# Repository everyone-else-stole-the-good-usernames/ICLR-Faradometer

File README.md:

```
_____     _       ____        _      ____      U  ___ u  __  __  U _____ u  _____  U _____ u   ____     
 |" ___|U  /"\  uU |  _"\ u U  /"\  u |  _"\      \/"_ \/U|' \/ '|u\| ___"|/ |_ " _| \| ___"|/U |  _"\ u  
U| |_  u \/ _ \/  \| |_) |/  \/ _ \/ /| | | |     | | | |\| |\/| |/ |  _|"     | |    |  _|"   \| |_) |/  
\|  _|/  / ___ \   |  _ <    / ___ \ U| |_| |\.-,_| |_| | | |  | |  | |___    /| |\   | |___    |  _ <    
 |_|    /_/   \_\  |_| \_\  /_/   \_\ |____/ u \_)-\___/  |_|  |_|  |_____|  u |_|U   |_____|   |_| \_\   
 )(\\,-  \\    >>  //   \\_  \\    >>  |||_         \\   <<,-,,-.   <<   >>  _// \\_  <<   >>   //   \\_  
(__)(_/ (__)  (__)(__)  (__)(__)  (__)(__)_)       (__)   (./  \.) (__) (__)(__) (__)(__) (__) (__)  (__) 

```

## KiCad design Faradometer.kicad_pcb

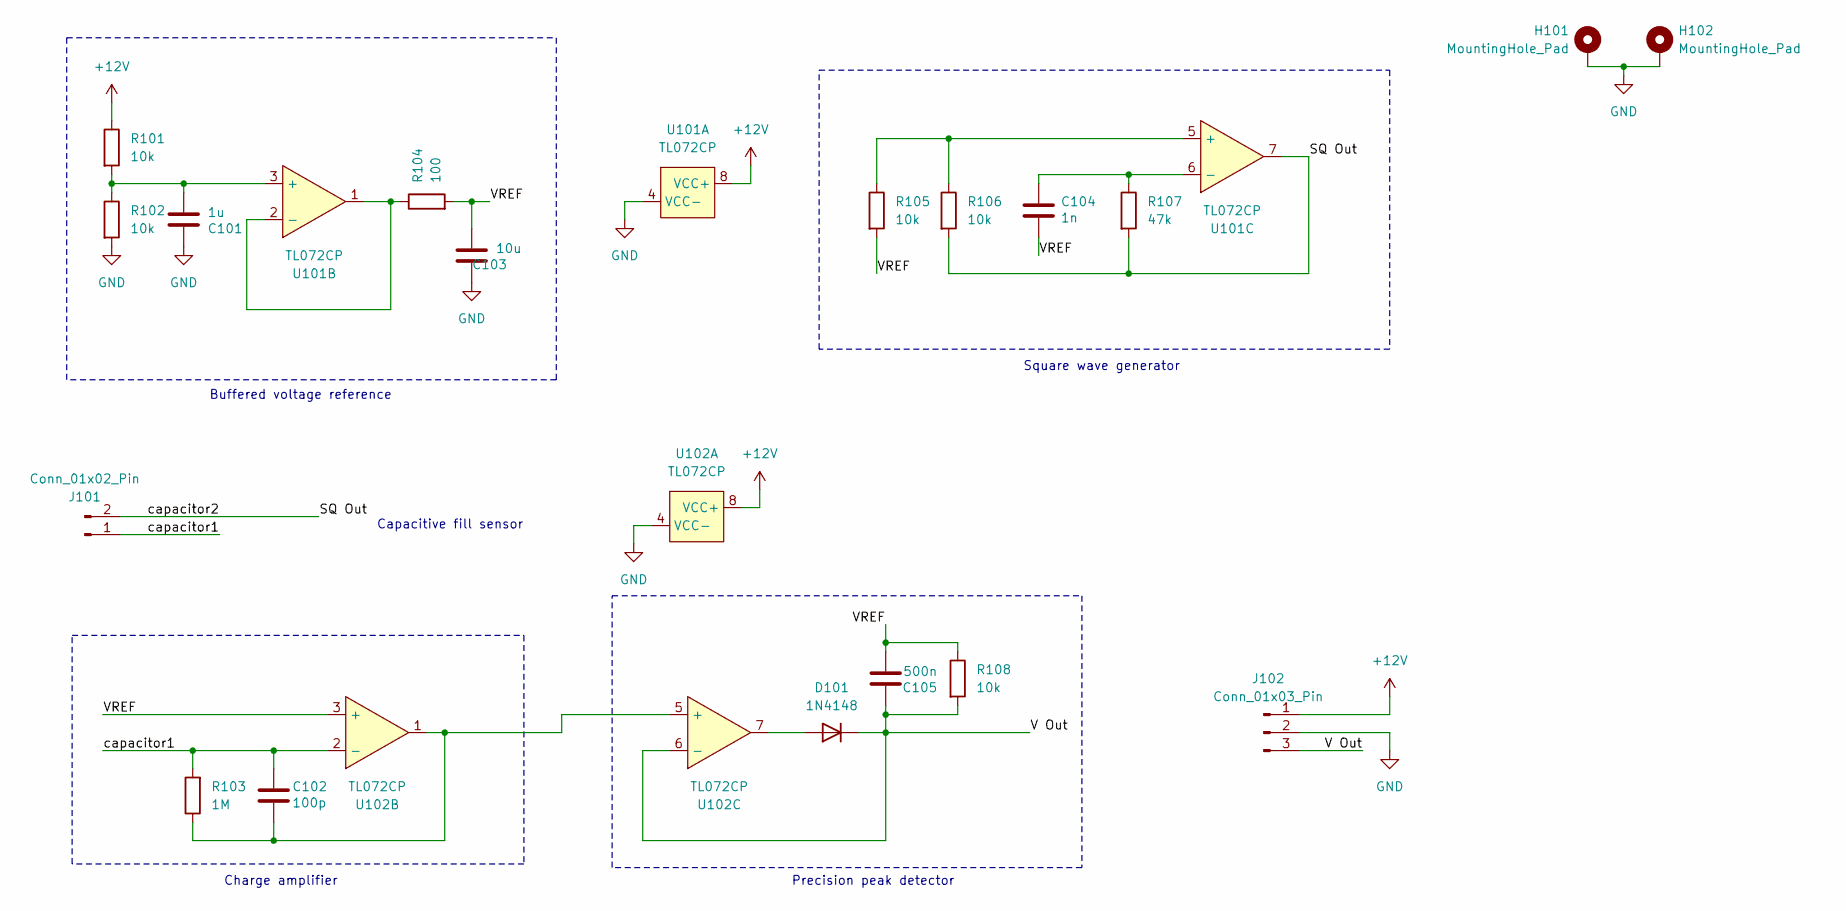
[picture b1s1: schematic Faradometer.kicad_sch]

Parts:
C101: 1u; C_0603_1608Metric_Pad1.08x0.95mm_HandSolder
C102: 100p; C_0402_1005Metric_Pad0.74x0.62mm_HandSolder
C103: 10u; C_0805_2012Metric_Pad1.18x1.45mm_HandSolder
C104: 1n; C_0402_1005Metric_Pad0.74x0.62mm_HandSolder
C105: 500n; C_0402_1005Metric_Pad0.74x0.62mm_HandSolder
D101: 1N4148; D_DO-35_SOD27_P7.62mm_Horizontal
H101, H102: MountingHole_Pad; MountingHole_3.2mm_M3_DIN965_Pad
J101: Conn_01x02_Pin; Molex_Nano-Fit_105313-xx02_1x02_P2.50mm_Horizontal
J102: Conn_01x03_Pin; Molex_Nano-Fit_105313-xx03_1x03_P2.50mm_Horizontal
R101, R102, R105, R106, R108: 10k; R_0805_2012Metric
R103: 1M; R_0805_2012Metric
R104: 100; R_0805_2012Metric
R107: 47k; R_0805_2012Metric
U101, U102: TL072CP; DIP-8_W7.62mm

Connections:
+12V: J102.1, R101.1, U101.8 (VCC+), U102.8 (VCC+); also elsewhere on the board
/SQ Out: J101.2, R106.2, R107.2, U101.7
/V Out: C105.1, D101.1 (K), J102.3, R108.2, U102.6 (-)
/VREF: C103.2, C104.1, C105.2, R104.2, R105.2, R108.1, U102.3 (+)
/capacitor1: C102.1, J101.1, R103.2, U102.2 (-)
GND: C101.1, C103.1, H101.1, H102.1, J102.2, R102.2, U101.4 (VCC-), U102.4 (VCC-); also elsewhere on the board
unnamed: D101.2 (A), U102.7
unnamed: C101.2, R101.2, R102.1, U101.3 (+)
unnamed: R104.1, U101.1, U101.2 (-)
unnamed: R105.1, R106.1, U101.5 (+)
unnamed: C104.2, R107.1, U101.6 (-)
unnamed: C102.2, R103.1, U102.1, U102.5 (+)

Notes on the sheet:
Capacitive fill sensor
Buffered voltage reference
Precision peak detector
Charge amplifier
Square wave generator

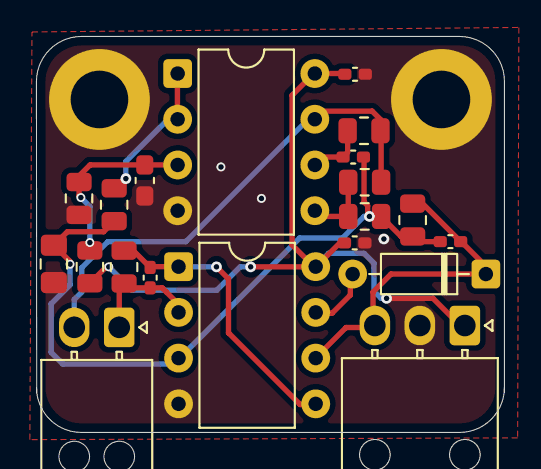
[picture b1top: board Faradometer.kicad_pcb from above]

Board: 2 copper layers, 26.0 x 22.0 mm, 22 parts (0 on the bottom side), 12 nets.

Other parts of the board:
C1, C2: 100nF; C_0402_1005Metric_Pad0.74x0.62mm_HandSolder

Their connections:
+12V: C1.1, C2.1; also elsewhere on the board
GND: C1.2, C2.2; also elsewhere on the board

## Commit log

2026-05-02 Add ASCII art to README.md
2026-05-02 change the symbols in schematic and made the pcb wirings
2026-06-05 Describe what you changed
2026-06-05 pcb reworked
2026-06-08 annotated schematic
2026-06-17 pcb change according to document
2026-06-17 Add .gitignore for KiCad junk files
2026-06-17 decoupling capacitor connection
2026-06-17 capacitor rearrangements
